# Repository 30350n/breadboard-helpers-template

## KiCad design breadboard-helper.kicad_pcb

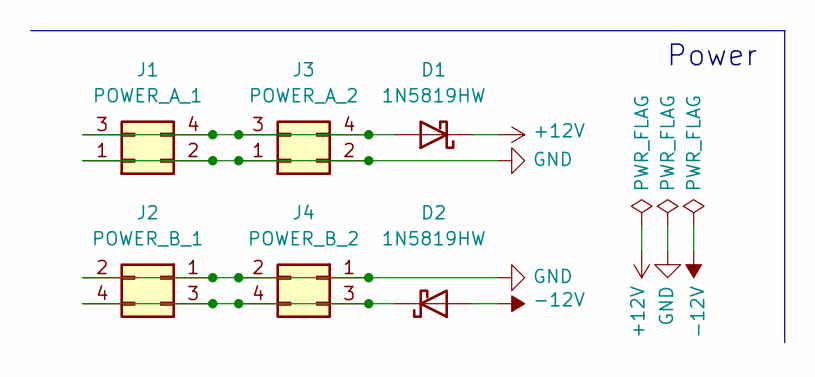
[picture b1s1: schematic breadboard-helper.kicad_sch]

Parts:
D1, D2: 1N5819HW; D_SOD-123
J1: POWER_A_1; PinHeader_2x02_P2.54mm_Vertical
J2: POWER_B_1; PinHeader_2x02_P2.54mm_Vertical
J3: POWER_A_2; PinHeader_2x02_P2.54mm_Vertical
J4: POWER_B_2; PinHeader_2x02_P2.54mm_Vertical

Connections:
+12V: D1.1 (K)
-12V: D2.2 (A)
GND: J1.1, J1.2, J2.1, J2.2, J3.1, J3.2, J4.1, J4.2
unnamed: D1.2 (A), J1.3, J1.4, J3.3, J3.4
unnamed: D2.1 (K), J2.3, J2.4, J4.3, J4.4

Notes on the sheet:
Power

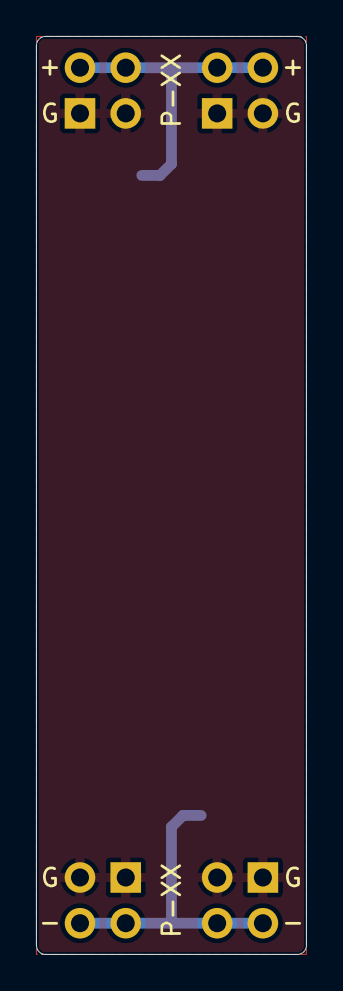
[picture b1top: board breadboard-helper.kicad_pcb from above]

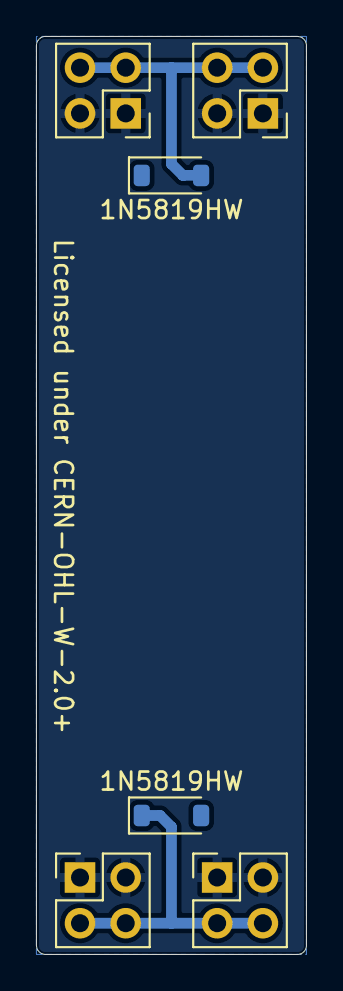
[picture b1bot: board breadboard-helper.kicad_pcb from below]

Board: 2 copper layers, 15.0 x 51.0 mm, 6 parts (6 on the bottom side), 3 nets.

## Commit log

2023-05-25 Add 1N5819HW diodes for reverse polarity protection
2023-05-25 Remove gitignore
2023-05-25 Add polarity markings
2023-05-25 Add local BreadboardHelpers library
2023-05-25 Set stackup colors, copper finish
2023-05-26 Adjust default plot settings

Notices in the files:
breadboard-helper.kicad_pcb:
Licensed under CERN-OHL-W-2.0+
